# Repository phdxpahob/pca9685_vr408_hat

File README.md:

# pca9685_vr408

This is a Raspberry Pi Hat with PCA9685PW. Design is based on the original Adafruit 16-Channel 12-bit PWM/Servo Driver with I2C interface, adapted for velleman spider robots. 

# WARNING

In revision A, there is an error in the design, VDD of the IC is not connected to the 3.3V rail of the Raspberry PI. This could be done using a wire bridge between the I2C Bus connector and the Via near C12. This is fixed in the current revision.

# Features and benefits:

- Both USB micro-B or terminal block power; 
- Can be powered directly from powerbank or another Pi HAT. 
- Split motor supply, extra capacitors to improve EMC. Tested with servos on all channels and the hat does not reset the Pi.
- Solder jumpers to change I2C address.
- Compatible with Adafruit libraries
- Header connects directly to the I2C pins & GPIO04 for O̅E̅ (Output enable). Even if GPIO is not configured the board is in output enable mode.
- Room for camera stand. (3D model is cam_stand.wrl)

# Limitations:

- No Reverse polarity protection! Keep in mind how you wire the terminal block!

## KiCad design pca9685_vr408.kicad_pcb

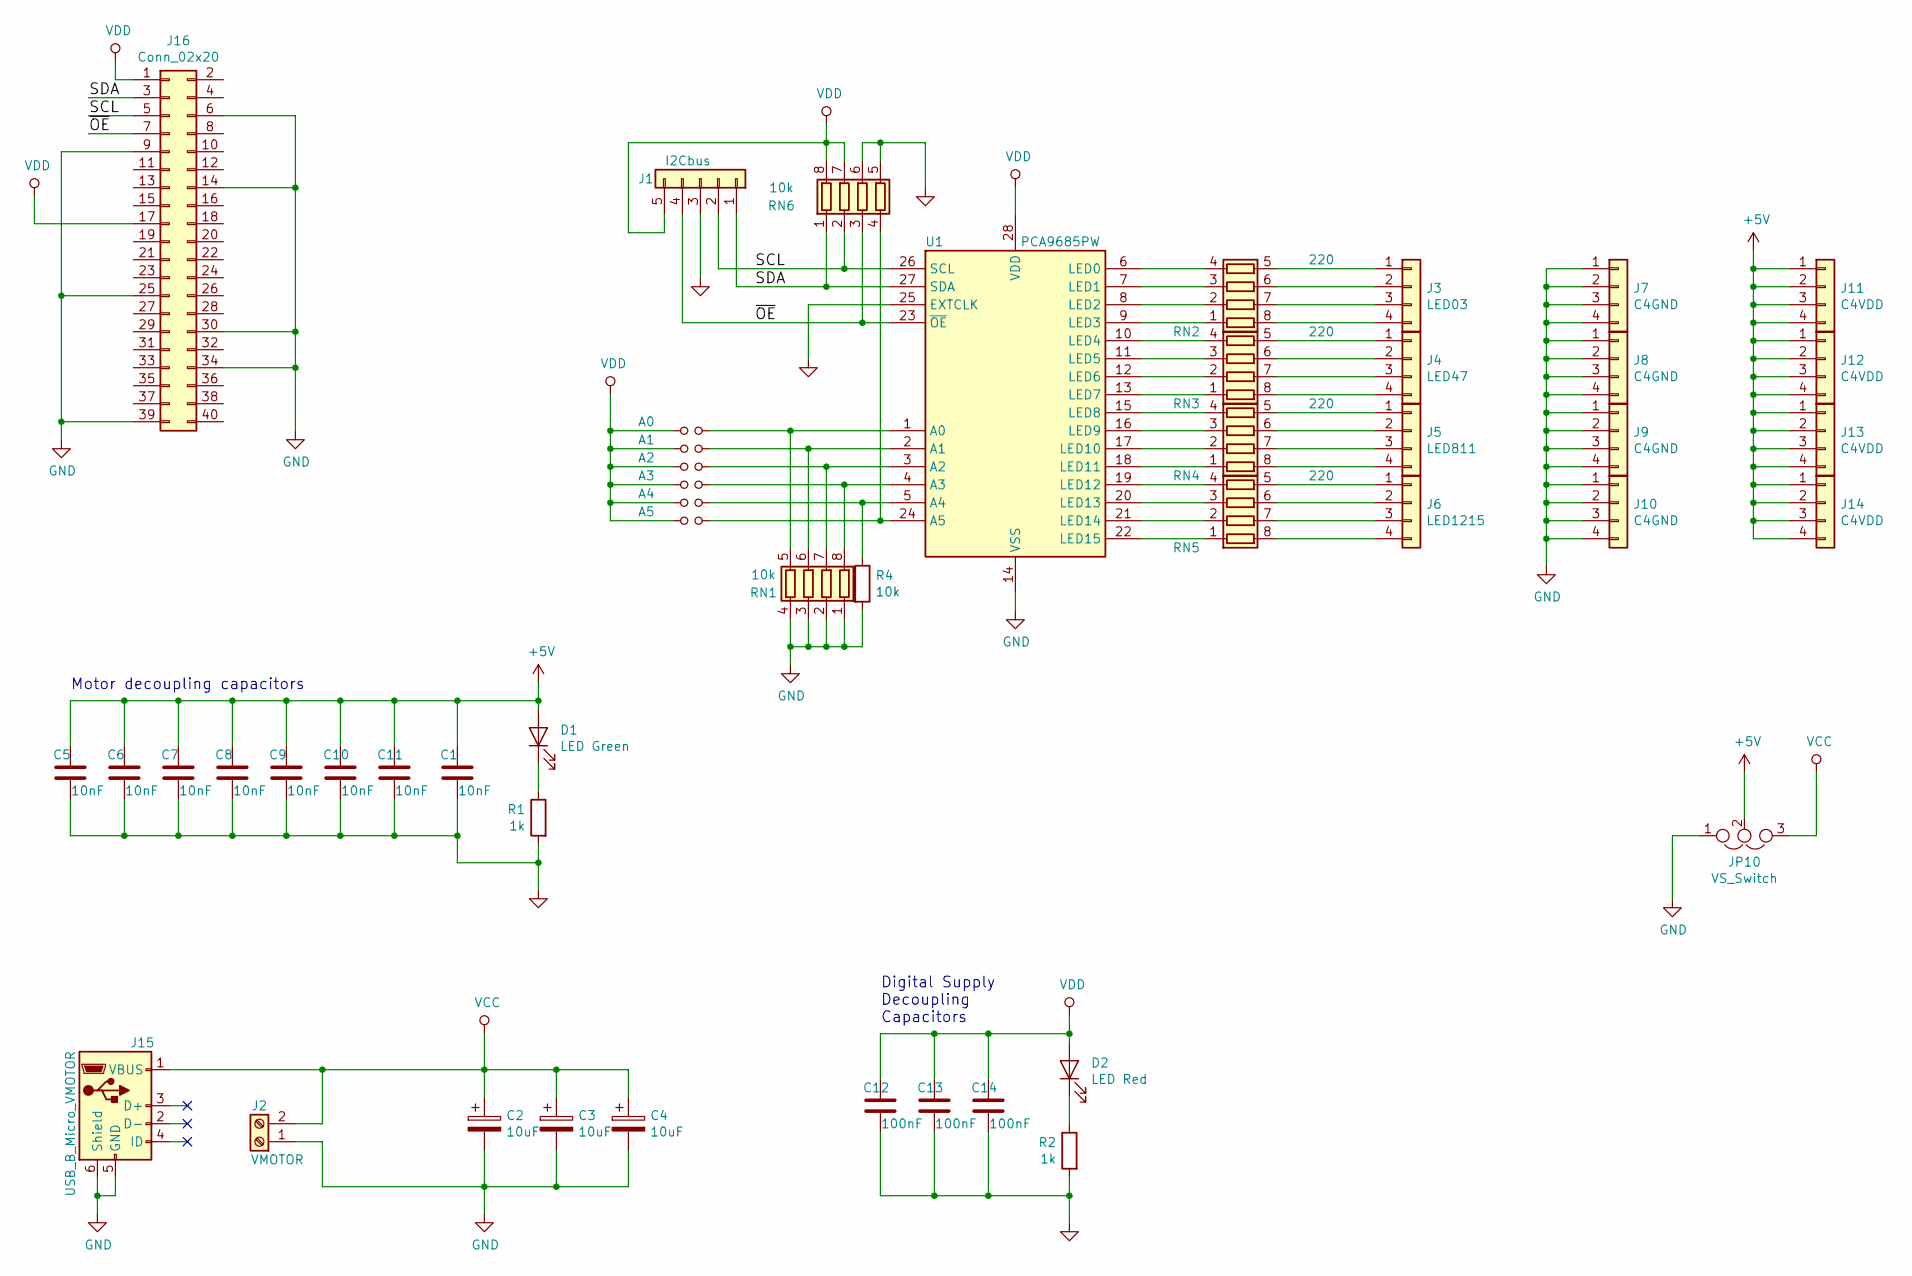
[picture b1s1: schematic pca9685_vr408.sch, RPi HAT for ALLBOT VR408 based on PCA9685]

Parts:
A0: A0; SolderJumper_Triangular_0603
A1: A1; SolderJumper_Triangular_0603
A2: A2; SolderJumper_Triangular_0603
A3: A3; SolderJumper_Triangular_0603
A4: A4; SolderJumper_Triangular_0603
A5: A5; SolderJumper_Triangular_0603
C1, C5, C6, C7, C8, C9, C10, C11: 10nF; C_0603_HandSoldering
C2, C3, C4: 10uF; CP_Elec_5x5.3
C12, C13, C14: 100nF; C_0603_HandSoldering
D1: LED Green; LED_0603_HandSoldering
D2: LED Red; LED_0603_HandSoldering
J1: I2Cbus; df13-5p-125ds
J2: VMOTOR; TerminalBlock_bornier-2_P5.08mm
J3: LED03; Pin_Header_Straight_1x04_Pitch2.54mm
J4: LED47; Pin_Header_Straight_1x04_Pitch2.54mm
J5: LED811; Pin_Header_Straight_1x04_Pitch2.54mm
J6: LED1215; Pin_Header_Straight_1x04_Pitch2.54mm
J7, J8, J9, J10: C4GND; Pin_Header_Straight_1x04_Pitch2.54mm
J11, J12, J13, J14: C4VDD; Pin_Header_Straight_1x04_Pitch2.54mm
J15: USB_B_Micro_VMOTOR; USB_Micro-B_Molex-105017-0001
J16: Conn_02x20; PinSocket_2x20_P2.54mm_Vertical
JP10: VS_Switch; Pin_Header_Straight_1x03_Pitch2.54mm
R1, R2: 1k; R_0603_HandSoldering
R4: 10k; R_0603_HandSoldering
RN1, RN6: 10k; R_Array_Convex_4x0603
RN2, RN3, RN4, RN5: 220; R_Array_Convex_4x0603
U1: PCA9685PW; TSSOP-28_4.4x9.7mm_Pitch0.65mm

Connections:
+5V: C1.1, C5.1, C6.1, C7.1, C8.1, C9.1, C10.1, C11.1, D1.2 (A), J11.1, J11.2, J11.3, J11.4, J12.1, J12.2, J12.3, J12.4, J13.1, J13.2, J13.3, J13.4, J14.1, J14.2, J14.3, J14.4, JP10.2
/SCL: J1.2, J16.5, RN6.2 (R2.1), U1.26 (SCL)
/SDA: J1.1, J16.3, RN6.1 (R1.1), U1.27 (SDA)
/~OE~: J1.4, J16.7, RN6.3 (R3.1), U1.23 (~OE)
GND: C1.2, C2.2, C3.2, C4.2, C5.2, C6.2, C7.2, C8.2, C9.2, C10.2, C11.2, C12.2, C13.2, C14.2, J1.3, J2.1, J7.1, J7.2, J7.3, J7.4, J8.1, J8.2, J8.3, J8.4, J9.1, J9.2, J9.3, J9.4, J10.1, J10.2, J10.3, J10.4, J15.5 (GND), J15.6 (Shield), J16.6, J16.9, J16.14, J16.25, J16.30, J16.34, J16.39, JP10.1, R1.2, R2.2, R4.2, RN1.1 (R1.1), RN1.2 (R2.1), RN1.3 (R3.1), RN1.4 (R4.1), RN6.5 (R4.2), RN6.6 (R3.2), U1.14 (VSS), U1.25 (EXTCLK)
unnamed: A0.2, RN1.5 (R4.2), U1.1 (A0)
unnamed: A1.2, RN1.6 (R3.2), U1.2 (A1)
unnamed: A2.2, RN1.7 (R2.2), U1.3 (A2)
unnamed: A3.2, RN1.8 (R1.2), U1.4 (A3)
unnamed: A4.2, R4.1, U1.5 (A4)
unnamed: A5.2, RN6.4 (R4.1), U1.24 (A5)
unnamed: D1.1 (K), R1.1
unnamed: D2.1 (K), R2.1
unnamed: J3.1, RN2.5 (R4.2)
unnamed: J3.2, RN2.6 (R3.2)
unnamed: J3.3, RN2.7 (R2.2)
unnamed: J3.4, RN2.8 (R1.2)
unnamed: J4.1, RN3.5 (R4.2)
unnamed: J4.2, RN3.6 (R3.2)
unnamed: J4.3, RN3.7 (R2.2)
unnamed: J4.4, RN3.8 (R1.2)
unnamed: J5.1, RN4.5 (R4.2)
unnamed: J5.2, RN4.6 (R3.2)
unnamed: J5.3, RN4.7 (R2.2)
unnamed: J5.4, RN4.8 (R1.2)
unnamed: J6.1, RN5.5 (R4.2)
unnamed: J6.2, RN5.6 (R3.2)
unnamed: J6.3, RN5.7 (R2.2)
unnamed: J6.4, RN5.8 (R1.2)
unnamed: RN2.1 (R1.1), U1.9 (LED3)
unnamed: RN2.2 (R2.1), U1.8 (LED2)
unnamed: RN2.3 (R3.1), U1.7 (LED1)
unnamed: RN2.4 (R4.1), U1.6 (LED0)
unnamed: RN3.1 (R1.1), U1.13 (LED7)
unnamed: RN3.2 (R2.1), U1.12 (LED6)
unnamed: RN3.3 (R3.1), U1.11 (LED5)
unnamed: RN3.4 (R4.1), U1.10 (LED4)
unnamed: RN4.1 (R1.1), U1.18 (LED11)
unnamed: RN4.2 (R2.1), U1.17 (LED10)
unnamed: RN4.3 (R3.1), U1.16 (LED9)
unnamed: RN4.4 (R4.1), U1.15 (LED8)
unnamed: RN5.1 (R1.1), U1.22 (LED15)
unnamed: RN5.2 (R2.1), U1.21 (LED14)
unnamed: RN5.3 (R3.1), U1.20 (LED13)
unnamed: RN5.4 (R4.1), U1.19 (LED12)
VCC: C2.1, C3.1, C4.1, J2.2, J15.1 (VBUS), JP10.3
VDD: A0.1, A1.1, A2.1, A3.1, A4.1, A5.1, C12.1, C13.1, C14.1, D2.2 (A), J1.5, J16.1, J16.17, RN6.7 (R2.2), RN6.8 (R1.2), U1.28 (VDD)

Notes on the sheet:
Motor decoupling capacitors
Digital Supply Decoupling Capacitors

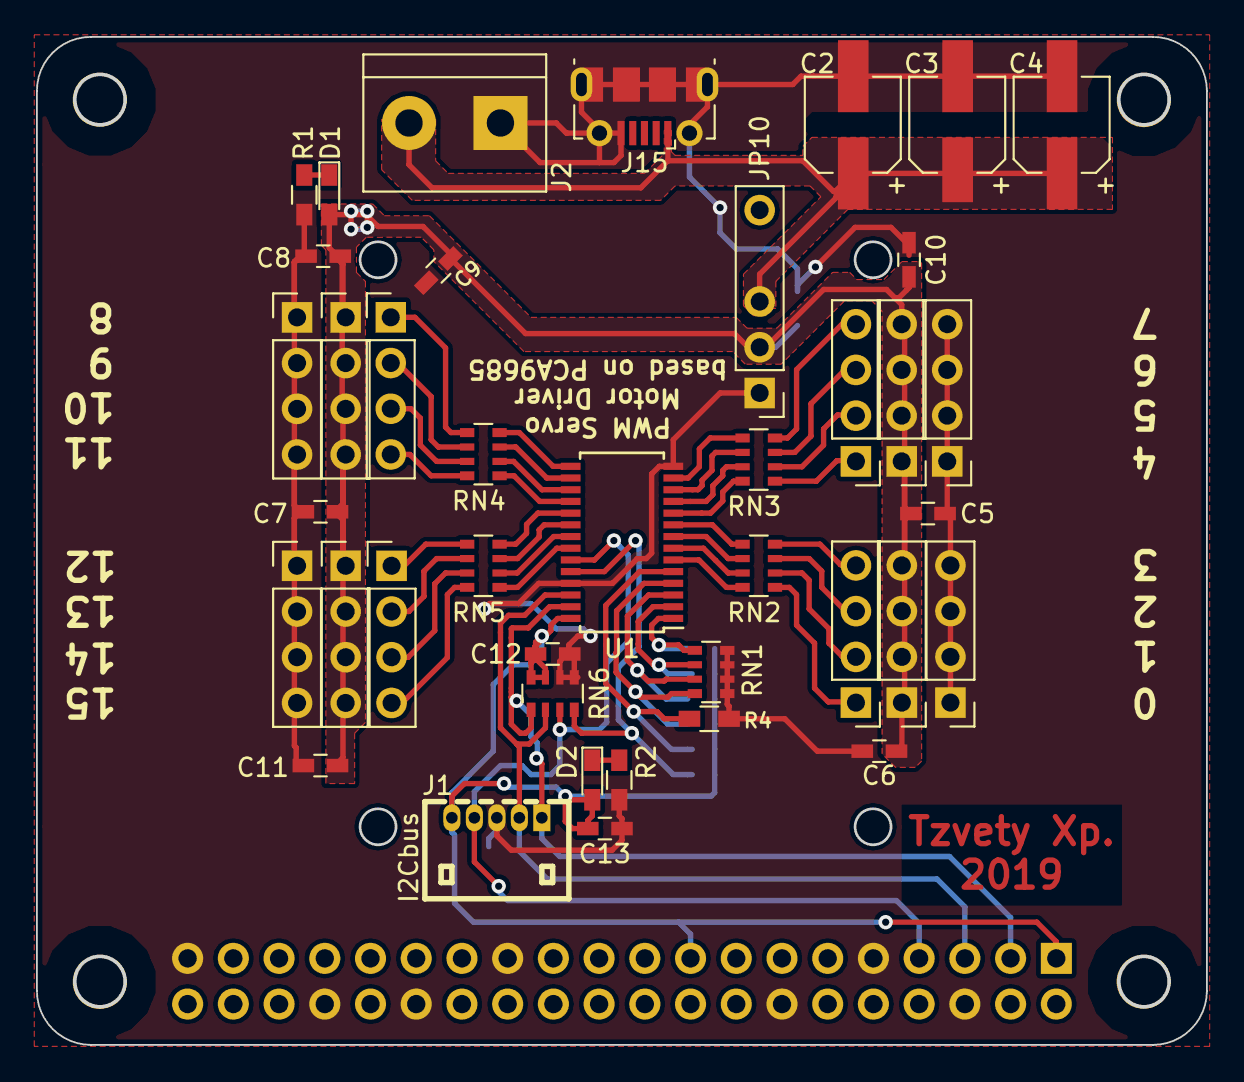
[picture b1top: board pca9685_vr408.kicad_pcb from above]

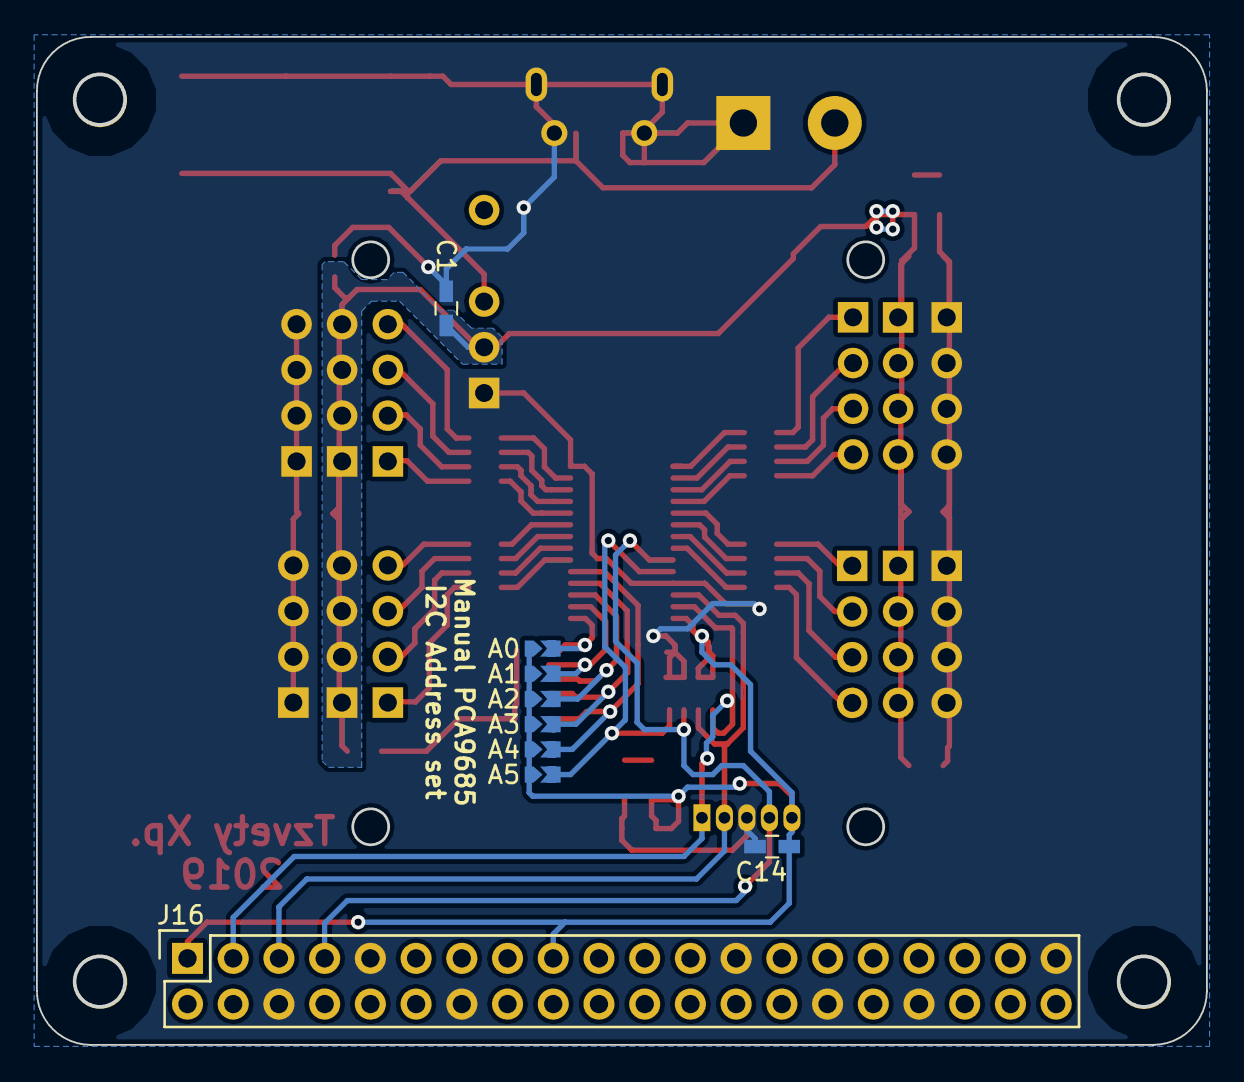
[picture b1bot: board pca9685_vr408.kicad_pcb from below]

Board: 2 copper layers, 64.9 x 55.9 mm, 53 parts (9 on the bottom side), 47 nets.

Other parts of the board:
H1, H2, H3, H4: 3mm_Mounting_Hole; NPTH_3mm_ID

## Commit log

2020-03-10 First commit
    Updated README.MD to have something to look at. Serious error about the design described.
2020-04-18 Update README.md
    Styling improvement.
2020-06-10 Updated layout
2020-07-19 Rename pca9685_vr412_2.kicad_pcb to revA/pca9685_vr412_2.kicad_pcb
2020-07-19 Rename fp-lib-table to revA/fp-lib-table
2020-07-19 Rename pca9685_vr412-cache.lib to revA/pca9685_vr412-cache.lib
2020-07-19 Rename pca9685_vr412.kicad_pcb to revA/pca9685_vr412.kicad_pcb
2020-07-19 Rename pca9685_vr412.net to revA/pca9685_vr412.net
2020-07-19 Rename pca9685_vr412.pro to revA/pca9685_vr412.pro
2020-07-19 Rename pca9685_vr412.sch to revA/pca9685_vr412.sch
2021-10-19 Update README.md
    Add board picture and some text clarification.
